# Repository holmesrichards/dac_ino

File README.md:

# dac/ino

This is a pair of boards and corresponding library which provide CV and gate I/O for an Arduino Nano. It is derived from [shaduzlabs/synapse](https://github.com/shaduzlabs/synapse), and there are obvious similarities to [ArdCore](http://20objects.com/ardcore/), but there are significant differences with both. 

There are two boards, dac/ino and dac/ino lite.

Differences between these and Synapse are:

- Board design with space for Arduino Nano, instead of as Uno style shield
- No on-board jacks — pads for Molex or pin connectors (or direct soldering) instead
- Simplification by eliminating software-controlled range selection
- Number of inputs and outputs is different
- dac/ino lite is battery powered and has 0–5 V output range, also uses Arduino Vcc as voltage reference

## Features
### dac/ino has
- 4 x control voltage inputs, 0 to 5V
- 2 x control voltage outputs, individually configurable as 0 to 5 V, 0 to 10 V, or -5 to 5 V via jumpers, with 12 bits of resolution
- 4 x gate inputs (with interrupt)
- 2 x gate outputs
- Additional inputs/outputs (direct connections to Arduino): 4 analog, 2 digital
- All above inputs/outputs connect via Molex connectors or solder pads, or via pin headers for daughterboards
- Voltage reference chip
- 1 x eurorack power connector (10 pin)

### dac/ino lite has
- 2 x control voltage outputs, 0 to 5 V, with 12 bits of resolution
- 1 x gate output
- Additional inputs/outputs (direct connections to Arduino): 4 analog, 2 digital
- All above inputs/outputs connect via Molex connectors or solder pads
- 6–12 V battery or unipolar power supply

## Compatible Arduinos
The PCB layout is for an Arduino Nano (5V).

## Dependencies
- [DirectIO](https://github.com/mmarchetti/DirectIO), for fast digital pin access

## Respository
- KiCad format schematics and PCB layouts, and Arduino library and example sketches, may be found at [https://github.com/holmesrichards/dac_ino](https://github.com/holmesrichards/dac_ino).

- [Build notes](docs/Build_notes.md)
- [dac/ino schematic](docs/dac_ino.pdf) (A bit confusing because the repetitive parts of the circuit are handled with KiCad heirarchical pages, so you have lots of pages with only a few components on each.)

- [dac/ino PCB layout](docs/dac_ino_pcb.pdf)

- [dac/ino BOM](docs/dac_ino_bom.md)

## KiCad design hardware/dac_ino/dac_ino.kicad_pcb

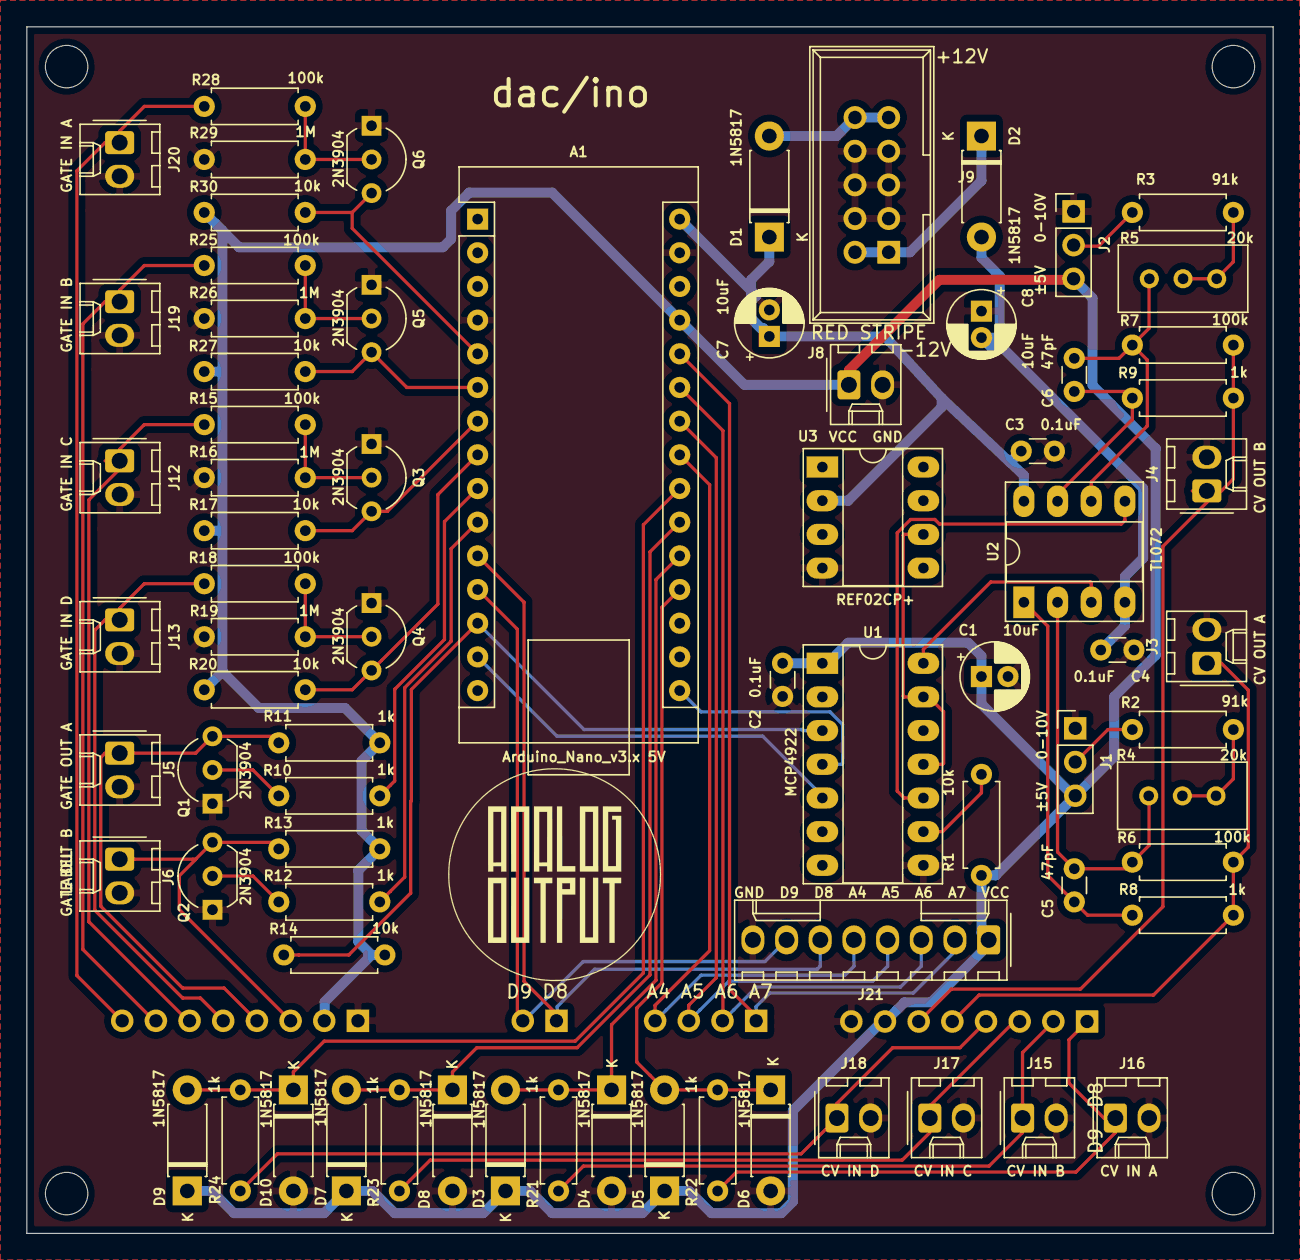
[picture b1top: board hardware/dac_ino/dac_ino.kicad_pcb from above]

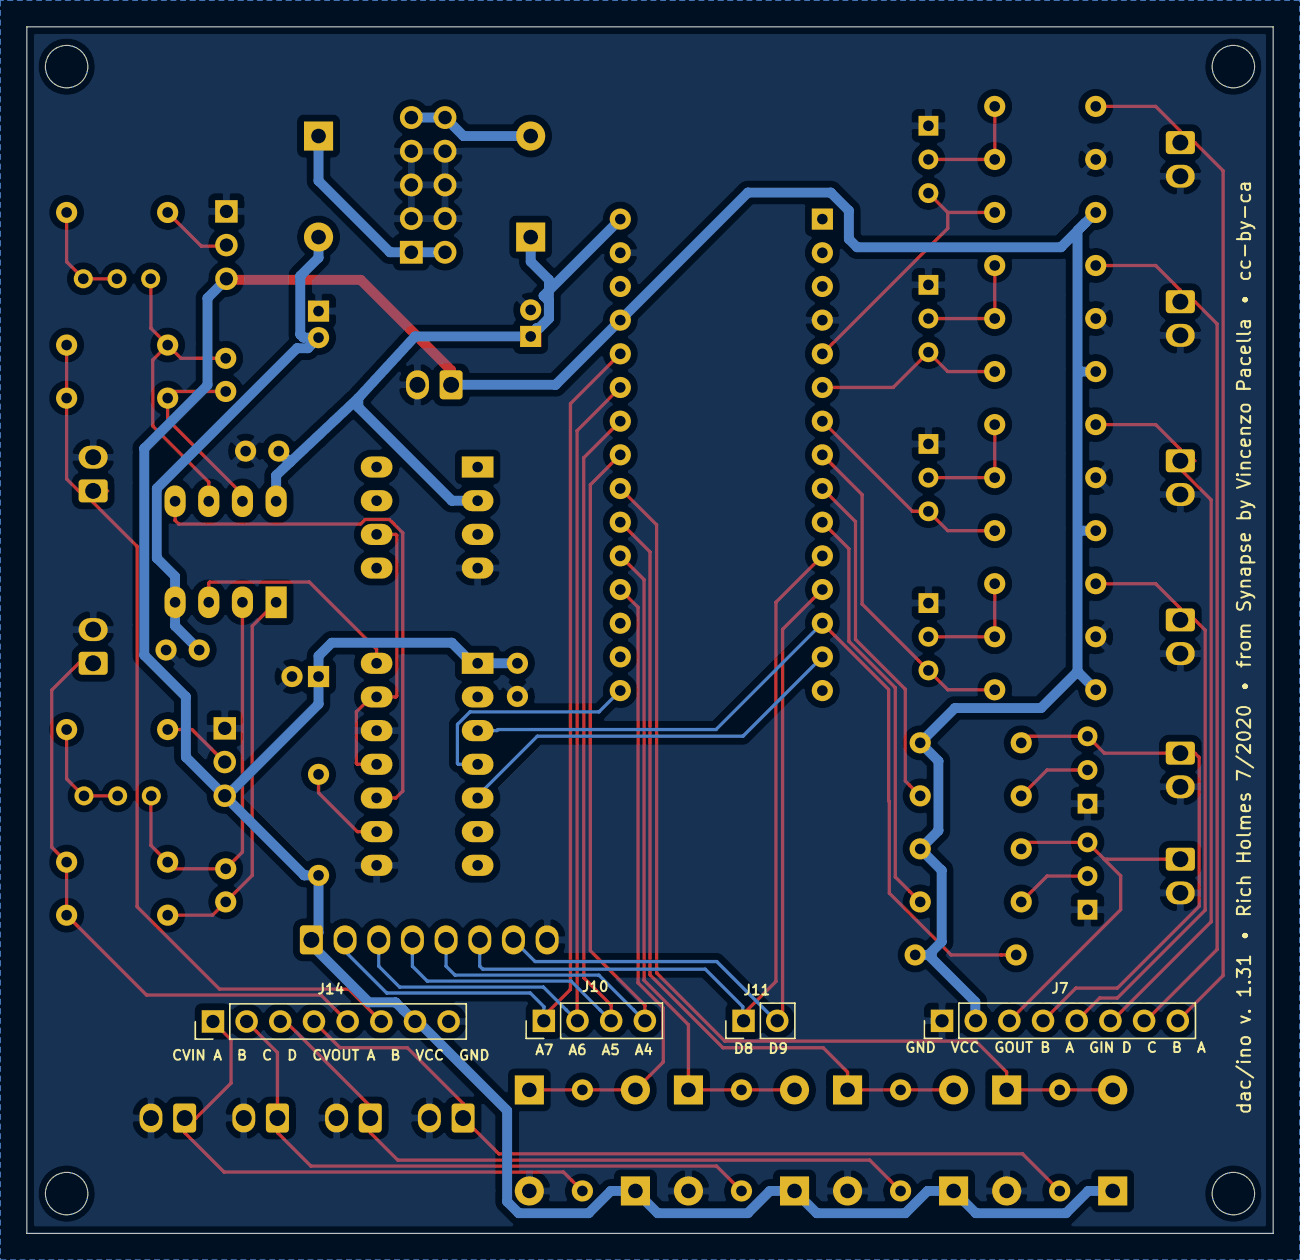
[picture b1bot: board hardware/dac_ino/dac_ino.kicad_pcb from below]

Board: 2 copper layers, 94.0 x 91.0 mm, 83 parts (4 on the bottom side), 55 nets.

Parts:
A1: Arduino_Nano_v3.x 5V; Arduino_Nano
C1, C7, C8: 10uF; CP_Radial_D5.0mm_P2.00mm
C2, C3, C4: 0.1uF; C_Disc_D3.0mm_W1.6mm_P2.50mm
C5, C6: 47pF; C_Disc_D3.0mm_W1.6mm_P2.50mm
D1, D2, D3, D4, D5, D6, D7, D8, D9, D10: 1N5817; D_DO-41_SOD81_P7.62mm_Horizontal
H1, H2, H3, H4: MountingHole; MountingHole_3.2mm_M3
J1, J2: Conn_01x03_Male; PinHeader_1x03_P2.54mm_Vertical
J3, J4: Molex 2 pin CV OUT; Molex_KK-254_AE-6410-02A_1x02_P2.54mm_Vertical
J5, J6: Molex 2 pin GATE OUT; Molex_KK-254_AE-6410-02A_1x02_P2.54mm_Vertical
J7, J14: Conn_01x01_Units; PinHeader_1x08_P2.54mm_Vertical
J8: Molex 2 pin VCC; Molex_KK-254_AE-6410-02A_1x02_P2.54mm_Vertical
J9: EURO_PWR_2x5; Power_Header
J10: Conn_01x04; PinHeader_1x04_P2.54mm_Vertical
J11: Conn_01x02; PinHeader_1x02_P2.54mm_Vertical
J12, J13, J19, J20: Molex 2 pin GATE IN; Molex_KK-254_AE-6410-02A_1x02_P2.54mm_Vertical
J15, J16, J17, J18: Molex 2 pin CV IN; Molex_KK-254_AE-6410-02A_1x02_P2.54mm_Vertical
J21: Conn_01x06; Molex_KK-254_AE-6410-08A_1x08_P2.54mm_Vertical
Q1, Q2, Q3, Q4, Q5, Q6: 2N3904; TO-92_Inline_Wide
R1, R14, R17, R20, R27, R30: 10k; R_Axial_DIN0207_L6.3mm_D2.5mm_P7.62mm_Horizontal
R2, R3: 91k; R_Axial_DIN0207_L6.3mm_D2.5mm_P7.62mm_Horizontal
R4, R5: 20k; Potentiometer_Bourns_3296W_Vertical
R6, R7, R15, R18, R25, R28: 100k; R_Axial_DIN0207_L6.3mm_D2.5mm_P7.62mm_Horizontal
R8, R9, R10, R11, R12, R13, R21, R22, R23, R24: 1k; R_Axial_DIN0207_L6.3mm_D2.5mm_P7.62mm_Horizontal
R16, R19, R26, R29: 1M; R_Axial_DIN0207_L6.3mm_D2.5mm_P7.62mm_Horizontal
U1: MCP4922; DIP-14_W7.62mm_Socket_LongPads
U2: TL072; DIP-8_W7.62mm_Socket_LongPads
U3: REF02CP+; DIP-8_W7.62mm_Socket_LongPads

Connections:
+VIN: A1.30, C3.1, C7.1, D1.1, U2.8, U3.2
-VIN: C4.2, C8.2, D2.2, U2.4
/Arduino/A0: A1.19, D5.2, D6.1, R22.1
/Arduino/A1: A1.20, D3.2, D4.1, R21.1
/Arduino/A2: A1.21, D7.2, D8.1, R23.1
/Arduino/A3: A1.22, D9.2, D10.1, R24.1
/Arduino/A4: A1.23, J10.4, J21.5
/Arduino/A5: A1.24, J10.3, J21.4
/Arduino/A6: A1.25, J10.2, J21.3
/Arduino/A7: A1.26, J10.1, J21.2
/Arduino/D2: A1.5, Q6.3, R30.1
/Arduino/D3: A1.6, Q5.3, R27.1
/Arduino/D4: A1.7, Q3.3, R17.1
/Arduino/D5: A1.8, Q4.3, R20.1
/Arduino/D6: A1.9, R10.2
/Arduino/D7: A1.10, R12.2
/Arduino/D8: A1.11, J11.1, J21.6
/Arduino/D9: A1.12, J11.2, J21.7
/Arduino/DAC_CS: A1.13, R14.2, U1.3
/Arduino/MOSI: A1.14, U1.5
/Arduino/SCK: A1.16, U1.4
/CV out/CV_OUT_A: J3.1, J14.5, R6.2, R8.2
/CV out/CV_OUT_B: J4.1, J14.6, R7.2, R9.2
/CV out/DAC_A: U1.14, U2.3
/CV out/DAC_B: U1.10, U2.5
/Gate out/GATE_OUT_A: J5.1, J7.4, Q1.3, R11.1
/Gate out/GATE_OUT_B: J6.1, J7.3, Q2.3, R13.1
/Inputs/CV IN D/CV_IN: J14.4, J18.1, R24.2
/Inputs/CV in A/CV_IN: J14.1, J16.1, R22.2
/Inputs/CV in B/CV_IN: J14.2, J15.1, R21.2
/Inputs/CV in C/CV_IN: J14.3, J17.1, R23.2
/Inputs/Gate in A/GATE_IN: J7.8, J20.1, R28.2
/Inputs/Gate in B/GATE_IN: J7.7, J19.1, R25.2
/Inputs/Gate in C/GATE_IN: J7.6, J12.1, R15.2
/Inputs/Gate in D/GATE_IN: J7.5, J13.1, R18.2
/Voltage reference/VREF: U1.11, U1.13, U3.6
GND: A1.4, A1.29, C1.2, C2.2, C3.2, C4.1, C7.2, C8.1, D4.2, D6.2, D8.2, D10.2, J1.1, J2.1, J3.2, J4.2, J5.2, J6.2, J7.1, J8.2, J9.3, J9.4, J9.5, J9.6, J9.7, J9.8, J12.2, J13.2, J14.8, J15.2, J16.2, J17.2, J18.2, J19.2, J20.2, J21.8, Q1.1, Q2.1, Q3.1, Q4.1, Q5.1, Q6.1, R16.1, R19.1, R26.1, R29.1, U1.8, U1.12, U3.4
unnamed: C5.1, R8.1, U2.1
unnamed: C5.2, R4.1, R6.1, U2.2
unnamed: C6.1, R9.1, U2.7
unnamed: C6.2, R5.1, R7.1, U2.6
unnamed: D1.2, J9.9, J9.10
unnamed: D2.1, J9.1, J9.2
unnamed: J1.2, R2.1
unnamed: J2.2, R3.1
unnamed: Q1.2, R10.1
unnamed: Q2.2, R12.1
unnamed: Q3.2, R15.1, R16.2
unnamed: Q4.2, R18.1, R19.2
unnamed: Q5.2, R25.1, R26.2
unnamed: Q6.2, R28.1, R29.2
unnamed: R1.2, U1.9
unnamed: R2.2, R4.2, R4.3
unnamed: R3.2, R5.2, R5.3
VCC: A1.27, C1.1, C2.1, D3.1, D5.1, D7.1, D9.1, J1.3, J2.3, J7.2, J8.1, J14.7, J21.1, R1.1, R11.2, R13.2, R14.1, R17.2, R20.2, R27.2, R30.2, U1.1

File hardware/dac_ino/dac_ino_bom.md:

# dac_ino BOM

Mon 04 May 2020 10:14:20 AM EDT

Generated from schematic by Eeschema 5.1.5-52549c5~84~ubuntu18.04.1

**Component Count:** 79

| Value | Qty | Part | Description | Vendor |
| ----- | --- | ---- | ----------- | ------ |
| A1 | 1 | Arduino_Nano_v3.x 5V | Arduino Nano v3.x |  |
| C1, C7, C8 | 3 | 10uF | Polarized capacitor |  |
| C2, C3, C4 | 3 | 0.1uF | Unpolarized capacitor |  |
| C5, C6 | 2 | 47pF | Unpolarized capacitor |  |
| D1, D2, D3, D4, D5, D6, D7, D8, D9, D10 | 10 | 1N5817 | 20V 1A Schottky Barrier Rectifier Diode, DO-41 |  |
| H1, H2, H3, H4 | 4 | MountingHole | Mounting Hole without connection |  |
| J1, J2 | 2 | Conn_01x03_Male | Generic connector, single row, 01x03, script generated (kicad-library-utils/schlib/autogen/connector/) |  |
| J3, J4, J5, J6 | 4 | Molex 2 pin | Generic connector, single row, 01x02, script generated (kicad-library-utils/schlib/autogen/connector/) |  |
| J7 | 1 | VCC | Generic connector, single row, 01x02, script generated (kicad-library-utils/schlib/autogen/connector/) |  |
| J8 | 1 | EURO_PWR_2x5 |  |  |
| J9 | 1 | Conn_01x04 | Generic connector, single row, 01x04, script generated (kicad-library-utils/schlib/autogen/connector/) |  |
| J10 | 1 | Conn_01x02 | Generic connector, single row, 01x02, script generated (kicad-library-utils/schlib/autogen/connector/) |  |
| J11, J12, J13, J14 | 4 | GATE IN | Generic connector, single row, 01x02, script generated (kicad-library-utils/schlib/autogen/connector/) |  |
| J15, J16, J17, J18 | 4 | CV IN | Generic connector, single row, 01x02, script generated (kicad-library-utils/schlib/autogen/connector/) |  |
| Q1, Q2, Q3, Q4, Q5, Q6 | 6 | 2N3904 | 0.2A Ic, 40V Vce, Small Signal NPN Transistor, TO-92 |  |
| R1, R14, R17, R20, R23, R26 | 6 | 10k | Resistor |  |
| R2, R3 | 2 | 91k | Resistor |  |
| R4, R5 | 2 | 20k | Trim-potentiometer |  |
| R6, R7, R15, R18, R21, R24 | 6 | 100k | Resistor |  |
| R8, R9, R10, R11, R12, R13, R27, R28, R29, R30 | 10 | 1k | Resistor |  |
| R16, R19, R22, R25 | 4 | 1M | Resistor |  |
| U1 | 1 | MCP4922 | 2-Channel 12-Bit D/A Converters with SPI Interface |  |
| U2 | 1 | TL072 | Dual Low-Noise JFET-Input Operational Amplifiers, DIP-8/SOIC-8 |  |

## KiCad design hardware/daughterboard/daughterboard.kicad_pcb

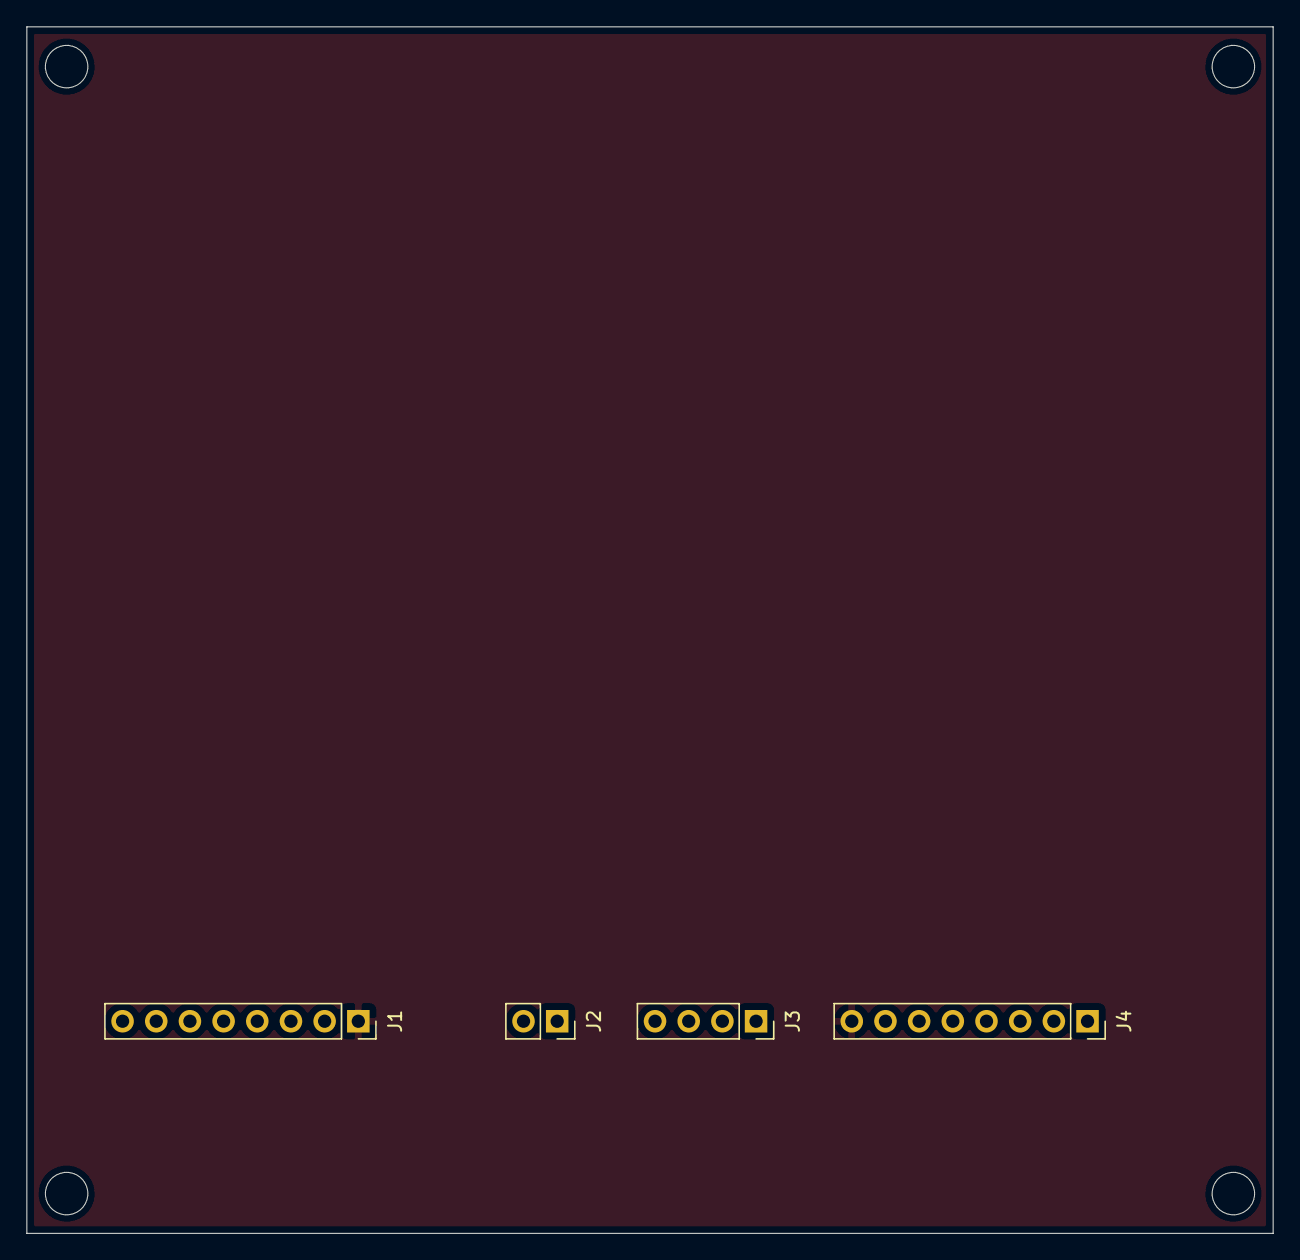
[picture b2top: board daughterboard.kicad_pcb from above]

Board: 2 copper layers, 94.0 x 91.0 mm, 8 parts (0 on the bottom side), 2 nets, no tracks yet.

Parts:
H1, H2, H3, H4: MountingHole; MountingHole_3.2mm_M3
J1, J4: Conn_01x08; PinSocket_1x08_P2.54mm_Vertical
J2: Conn_01x02; PinSocket_1x02_P2.54mm_Vertical
J3: Conn_01x04; PinSocket_1x04_P2.54mm_Vertical

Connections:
GND: J1.1, J4.8
VCC: J1.2, J4.7

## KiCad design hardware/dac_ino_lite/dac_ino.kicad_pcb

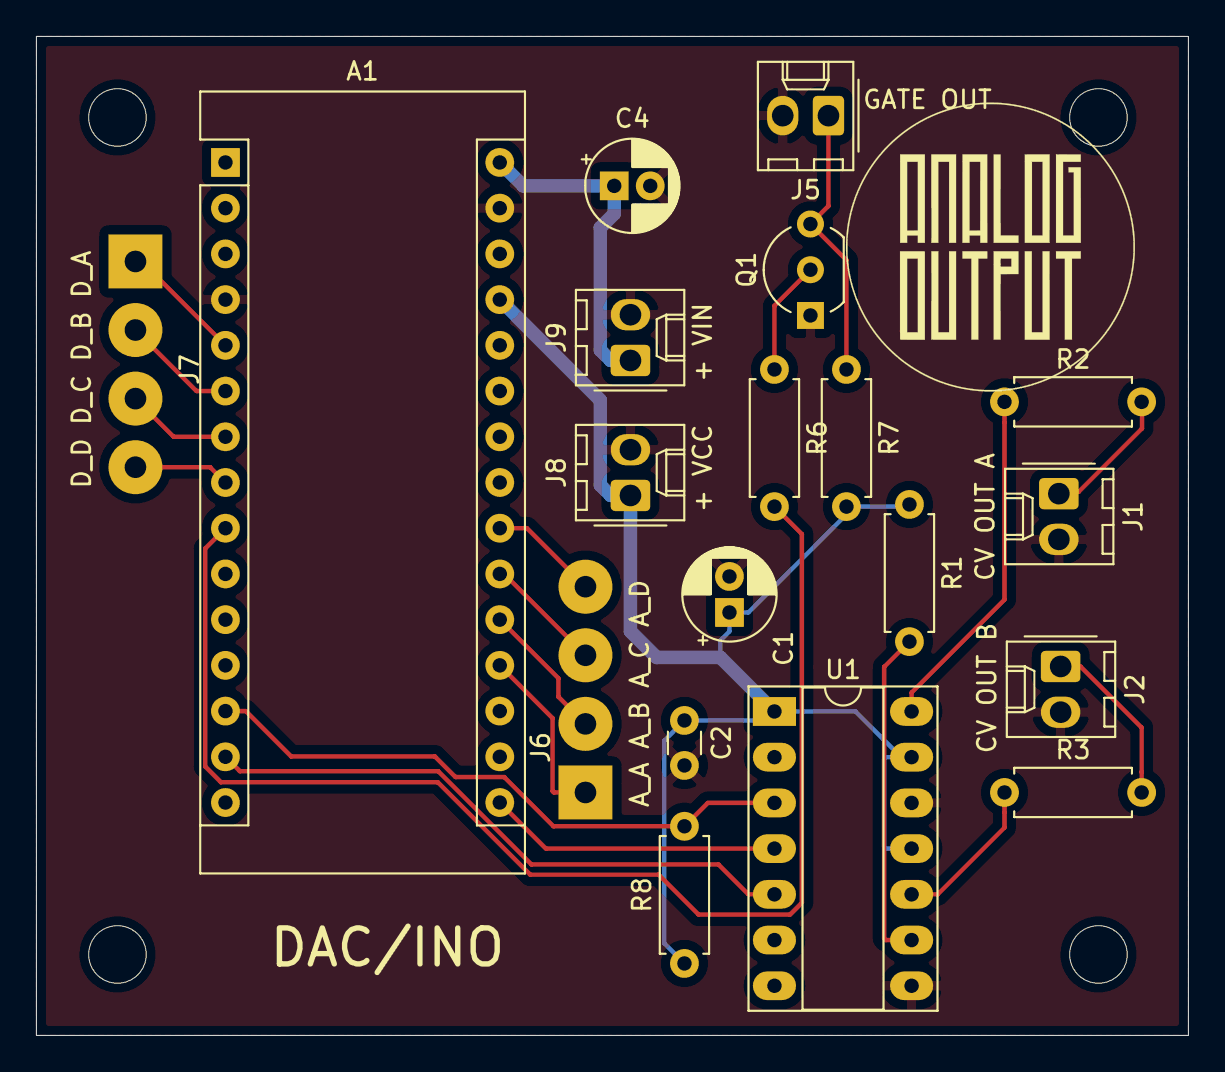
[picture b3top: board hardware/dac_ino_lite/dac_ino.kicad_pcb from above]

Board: 2 copper layers, 64.0 x 55.5 mm, 23 parts (0 on the bottom side), 22 nets.

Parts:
A1: Arduino_Nano_v3.x 5V; Arduino_Nano
C1, C4: 10uF; CP_Radial_D5.0mm_P2.00mm
C2: 0.1uF; C_Disc_D3.0mm_W1.6mm_P2.50mm
H1, H2, H3, H4: MountingHole; MountingHole_3.2mm_M3
J1: CV OUT A; Molex_KK-254_AE-6410-02A_1x02_P2.54mm_Vertical
J2: CV OUT B; Molex_KK-254_AE-6410-02A_1x02_P2.54mm_Vertical
J5: GATE OUT A; Molex_KK-254_AE-6410-02A_1x02_P2.54mm_Vertical
J6, J7: Conn_01x04; SolderWirePad_1x04_P3.81mm_Drill1.2mm
J8: VCC; Molex_KK-254_AE-6410-02A_1x02_P2.54mm_Vertical
J9: Vin; Molex_KK-254_AE-6410-02A_1x02_P2.54mm_Vertical
Q1: 2N3904; TO-92_Inline_Wide
R1, R8: 10K; R_Axial_DIN0207_L6.3mm_D2.5mm_P7.62mm_Horizontal
R2, R3: 1K; R_Axial_DIN0207_L6.3mm_D2.5mm_P7.62mm_Horizontal
R6, R7: 1k; R_Axial_DIN0207_L6.3mm_D2.5mm_P7.62mm_Horizontal
U1: MCP4922; DIP-14_W7.62mm_Socket_LongPads

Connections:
+VIN: A1.30, C4.1, J9.1
/Arduino/A_IN_A: A1.19, J6.1
/Arduino/A_IN_B: A1.20, J6.2
/Arduino/A_IN_C: A1.21, J6.3
/Arduino/A_IN_D: A1.22, J6.4
/Arduino/DAC_CS: A1.13, R8.2, U1.3
/Arduino/D_IN_A: A1.5, J7.1
/Arduino/D_IN_B: A1.6, J7.2
/Arduino/D_IN_C: A1.7, J7.3
/Arduino/D_IN_D: A1.8, J7.4
/Arduino/D_OUT_A: A1.9, R6.2
/Arduino/MOSI: A1.14, U1.5
/Arduino/SCK: A1.16, U1.4
/DAC/CV_OUT_A: J1.1, R2.2
/DAC/CV_OUT_B: J2.1, R3.2
/Gate out/GATE_OUT: J5.1, Q1.3, R7.1
GND: A1.4, A1.29, C1.2, C2.2, C4.2, J1.2, J2.2, J5.2, J8.2, J9.2, Q1.1, U1.8, U1.12
unnamed: Q1.2, R6.1
unnamed: R1.2, U1.9
unnamed: R2.1, U1.14
unnamed: R3.1, U1.10
VCC: A1.27, C1.1, C2.1, J8.1, R1.1, R7.2, R8.1, U1.1, U1.11, U1.13

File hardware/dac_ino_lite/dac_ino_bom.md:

# dac_ino BOM

Mon 04 May 2020 10:25:07 AM EDT

Generated from schematic by Eeschema 5.1.5-52549c5~84~ubuntu18.04.1

**Component Count:** 23

| Value | Qty | Part | Description | Vendor |
| ----- | --- | ---- | ----------- | ------ |
| A1 | 1 | Arduino_Nano_v3.x 5V | Arduino Nano v3.x |  |
| C1, C4 | 2 | 10uF | Polarized capacitor |  |
| C2 | 1 | 0.1uF | Unpolarized capacitor |  |
| H1, H2, H3, H4 | 4 | MountingHole | Mounting Hole without connection |  |
| J1 | 1 | CV OUT A | Generic connector, single row, 01x02, script generated (kicad-library-utils/schlib/autogen/connector/) |  |
| J2 | 1 | CV OUT B | Generic connector, single row, 01x02, script generated (kicad-library-utils/schlib/autogen/connector/) |  |
| J5 | 1 | GATE OUT A | Generic connector, single row, 01x02, script generated (kicad-library-utils/schlib/autogen/connector/) |  |
| J6, J7 | 2 | Conn_01x04 | Generic connector, single row, 01x04, script generated (kicad-library-utils/schlib/autogen/connector/) |  |
| J8 | 1 | VCC | Generic connector, single row, 01x02, script generated (kicad-library-utils/schlib/autogen/connector/) |  |
| J9 | 1 | Vin | Generic connector, single row, 01x02, script generated (kicad-library-utils/schlib/autogen/connector/) |  |
| Q1 | 1 | 2N3904 | 0.2A Ic, 40V Vce, Small Signal NPN Transistor, TO-92 |  |
| R1, R8 | 2 | 10k | Resistor |  |
| R2, R3, R6, R7 | 4 | 1k | Resistor |  |
| U1 | 1 | MCP4922 | 2-Channel 12-Bit D/A Converters with SPI Interface |  |

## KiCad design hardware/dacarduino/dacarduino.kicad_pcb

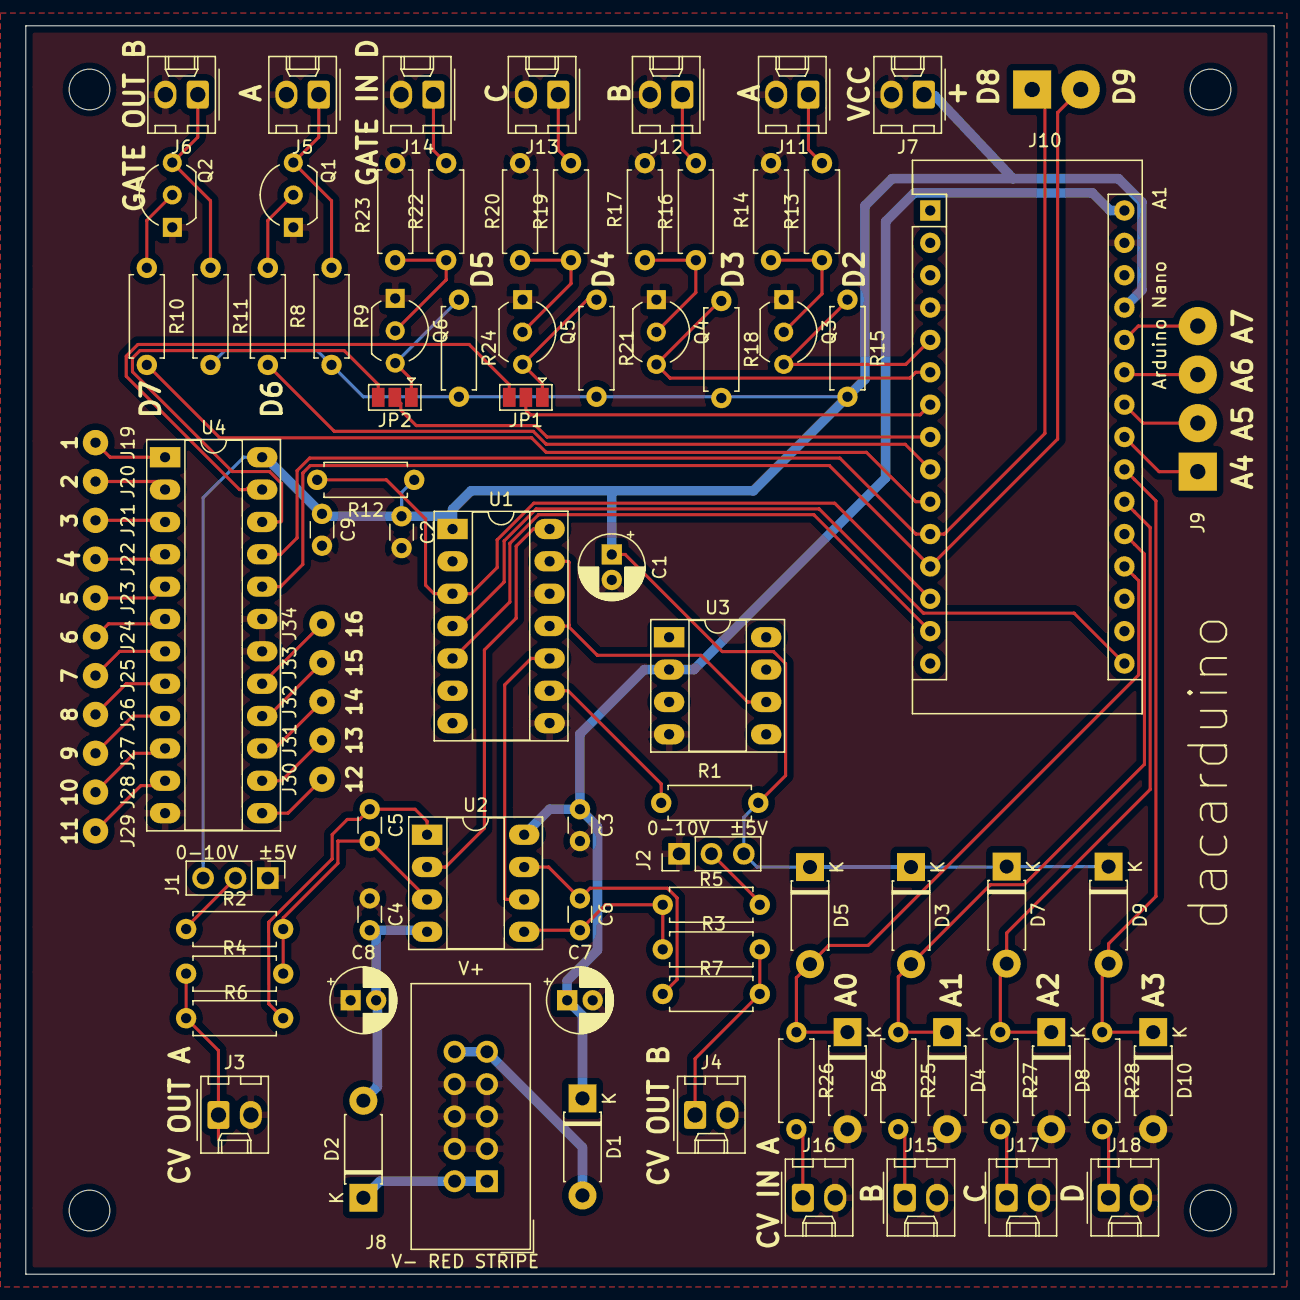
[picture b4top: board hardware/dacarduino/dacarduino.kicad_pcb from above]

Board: 2 copper layers, 98.0 x 98.0 mm, 98 parts (0 on the bottom side), 73 nets.

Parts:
A1: Arduino_Nano_v3.x 5V; Arduino_Nano
C1, C7, C8: 10uF; CP_Radial_D5.0mm_P2.00mm
C2, C3, C4, C9: 0.1uF; C_Disc_D3.0mm_W1.6mm_P2.50mm
C5, C6: 47pF; C_Disc_D3.0mm_W1.6mm_P2.50mm
D1, D2, D3, D4, D5, D6, D7, D8, D9, D10: 1N5817; D_DO-41_SOD81_P7.62mm_Horizontal
H1, H2, H3, H4: MountingHole; MountingHole_3.2mm_M3
J1, J2: Conn_01x03_Male; PinHeader_1x03_P2.54mm_Vertical
J3, J4, J5, J6: Molex 2 pin; Molex_KK-254_AE-6410-02A_1x02_P2.54mm_Vertical
J7: VCC; Molex_KK-254_AE-6410-02A_1x02_P2.54mm_Vertical
J8: EURO_PWR_2x5; IDC-Header_2x05_P2.54mm_Vertical
J9: Conn_01x04; SolderWirePad_1x04_P3.81mm_Drill1.2mm
J10: Conn_01x02; SolderWirePad_1x02_P3.81mm_Drill1.2mm
J11, J12, J13, J14: GATE IN; Molex_KK-254_AE-6410-02A_1x02_P2.54mm_Vertical
J15, J16, J17, J18: CV IN; Molex_KK-254_AE-6410-02A_1x02_P2.54mm_Vertical
J19, J20, J21, J22, J23, J24, J25, J26, J27, J28, J29, J30, J31, J32, J33, J34: Conn_01x01; SolderWirePad_1x01_Drill0.8mm
JP1, JP2: SolderJumper_3_Open; SolderJumper-3_P1.3mm_Open_Pad1.0x1.5mm
Q1, Q2, Q3, Q4, Q5, Q6: 2N3904; TO-92_Inline_Wide
R1, R12: 10K; R_Axial_DIN0207_L6.3mm_D2.5mm_P7.62mm_Horizontal
R2, R3, R4, R5: 100K; R_Axial_DIN0207_L6.3mm_D2.5mm_P7.62mm_Horizontal
R6, R7: 1K; R_Axial_DIN0207_L6.3mm_D2.5mm_P7.62mm_Horizontal
R8, R9, R10, R11, R25, R26, R27, R28: 1k; R_Axial_DIN0207_L6.3mm_D2.5mm_P7.62mm_Horizontal
R13, R16, R19, R22: 100k; R_Axial_DIN0207_L6.3mm_D2.5mm_P7.62mm_Horizontal
R14, R17, R20, R23: 1M; R_Axial_DIN0207_L6.3mm_D2.5mm_P7.62mm_Horizontal
R15, R18, R21, R24: 10k; R_Axial_DIN0207_L6.3mm_D2.5mm_P7.62mm_Horizontal
U1: MCP4922; DIP-14_W7.62mm_Socket_LongPads
U2: TL072; DIP-8_W7.62mm_Socket_LongPads
U3: REF02CP+; DIP-8_W7.62mm_Socket_LongPads
U4: SN74LS154N; DIP-24_W7.62mm_Socket_LongPads

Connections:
+VIN: A1.30, C3.1, C7.1, D1.1, U2.8, U3.2
-VIN: C4.2, C8.2, D2.2, U2.4
/Arduino/A0: A1.19, D5.2, D6.1, R26.1
/Arduino/A1: A1.20, D3.2, D4.1, R25.1
/Arduino/A2: A1.21, D7.2, D8.1, R27.1
/Arduino/A3: A1.22, D9.2, D10.1, R28.1
/Arduino/A4: A1.23, J9.1
/Arduino/A5: A1.24, J9.2
/Arduino/A6: A1.25, J9.3
/Arduino/A7: A1.26, J9.4
/Arduino/D2: A1.5, Q3.3, R15.1
/Arduino/D3: A1.6, Q4.3, R18.1
/Arduino/D4: A1.7, JP1.2
/Arduino/D5: A1.8, JP2.2
/Arduino/D6: A1.9, R8.2
/Arduino/D7: A1.10, R10.2
/Arduino/D8: A1.11, J10.1, U4.21
/Arduino/D9: A1.12, J10.2, U4.20
/Arduino/DAC_CS: A1.13, R12.2, U1.3
/Arduino/MOSI: A1.14, U1.5
/Arduino/SCK: A1.16, U1.4
/CV out/CV_OUT_A: J3.1, R4.2, R6.2
/CV out/CV_OUT_B: J4.1, R5.2, R7.2
/CV out/DAC_A: U1.14, U2.2
/CV out/DAC_B: U1.10, U2.6
/Gate out/GATE_OUT_A: J5.1, Q1.3, R9.1
/Gate out/GATE_OUT_B: J6.1, Q2.3, R11.1
/Inputs/CV IN D/CV_IN: J18.1, R28.2
/Inputs/CV in A/CV_IN: J16.1, R26.2
/Inputs/CV in B/CV_IN: J15.1, R25.2
/Inputs/CV in C/CV_IN: J17.1, R27.2
/Inputs/Gate in A/GATE_IN: J11.1, R13.2
/Inputs/Gate in B/GATE_IN: J12.1, R16.2
/Inputs/Gate in C/D_IN: JP1.1, Q5.3, R21.1
/Inputs/Gate in C/GATE_IN: J13.1, R19.2
/Inputs/Gate in D/D_IN: JP2.1, Q6.3, R24.1
/Inputs/Gate in D/GATE_IN: J14.1, R22.2
/Voltage reference/VREF: U1.11, U1.13, U3.6
GND: A1.4, A1.29, C1.2, C2.2, C3.2, C4.1, C7.2, C8.1, C9.2, D4.2, D6.2, D8.2, D10.2, J1.1, J2.1, J3.2, J4.2, J5.2, J6.2, J7.2, J8.3, J8.4, J8.5, J8.6, J8.7, J8.8, J11.2, J12.2, J13.2, J14.2, J15.2, J16.2, J17.2, J18.2, Q1.1, Q2.1, Q3.1, Q4.1, Q5.1, Q6.1, R14.1, R17.1, R20.1, R23.1, U1.8, U1.12, U3.4, U4.12, U4.18, U4.19
unnamed: C5.1, R6.1, U2.1
unnamed: C5.2, R2.2, R4.1, U2.3
unnamed: C6.1, R7.1, U2.7
unnamed: C6.2, R3.2, R5.1, U2.5
unnamed: D1.2, J8.9, J8.10
unnamed: D2.1, J8.1, J8.2
unnamed: J1.2, R2.1
unnamed: J2.2, R3.1
unnamed: J19.1, U4.1
unnamed: J20.1, U4.2
unnamed: J21.1, U4.3
unnamed: J22.1, U4.4
unnamed: J23.1, U4.5
unnamed: J24.1, U4.6
unnamed: J25.1, U4.7
unnamed: J26.1, U4.8
unnamed: J27.1, U4.9
unnamed: J28.1, U4.10
unnamed: J29.1, U4.11
unnamed: J30.1, U4.13
unnamed: J31.1, U4.14
unnamed: J32.1, U4.15
unnamed: J33.1, U4.16
unnamed: J34.1, U4.17
unnamed: JP1.3, U4.23
unnamed: JP2.3, U4.22
unnamed: Q1.2, R8.1
unnamed: Q2.2, R10.1
unnamed: Q3.2, R13.1, R14.2
unnamed: Q4.2, R16.1, R17.2
unnamed: Q5.2, R19.1, R20.2
unnamed: Q6.2, R22.1, R23.2
unnamed: R1.2, U1.9
VCC: A1.27, C1.1, C2.1, C9.1, D3.1, D5.1, D7.1, D9.1, J1.3, J2.3, J7.1, R1.1, R9.2, R11.2, R12.1, R15.2, R18.2, R21.2, R24.2, U1.1, U4.24

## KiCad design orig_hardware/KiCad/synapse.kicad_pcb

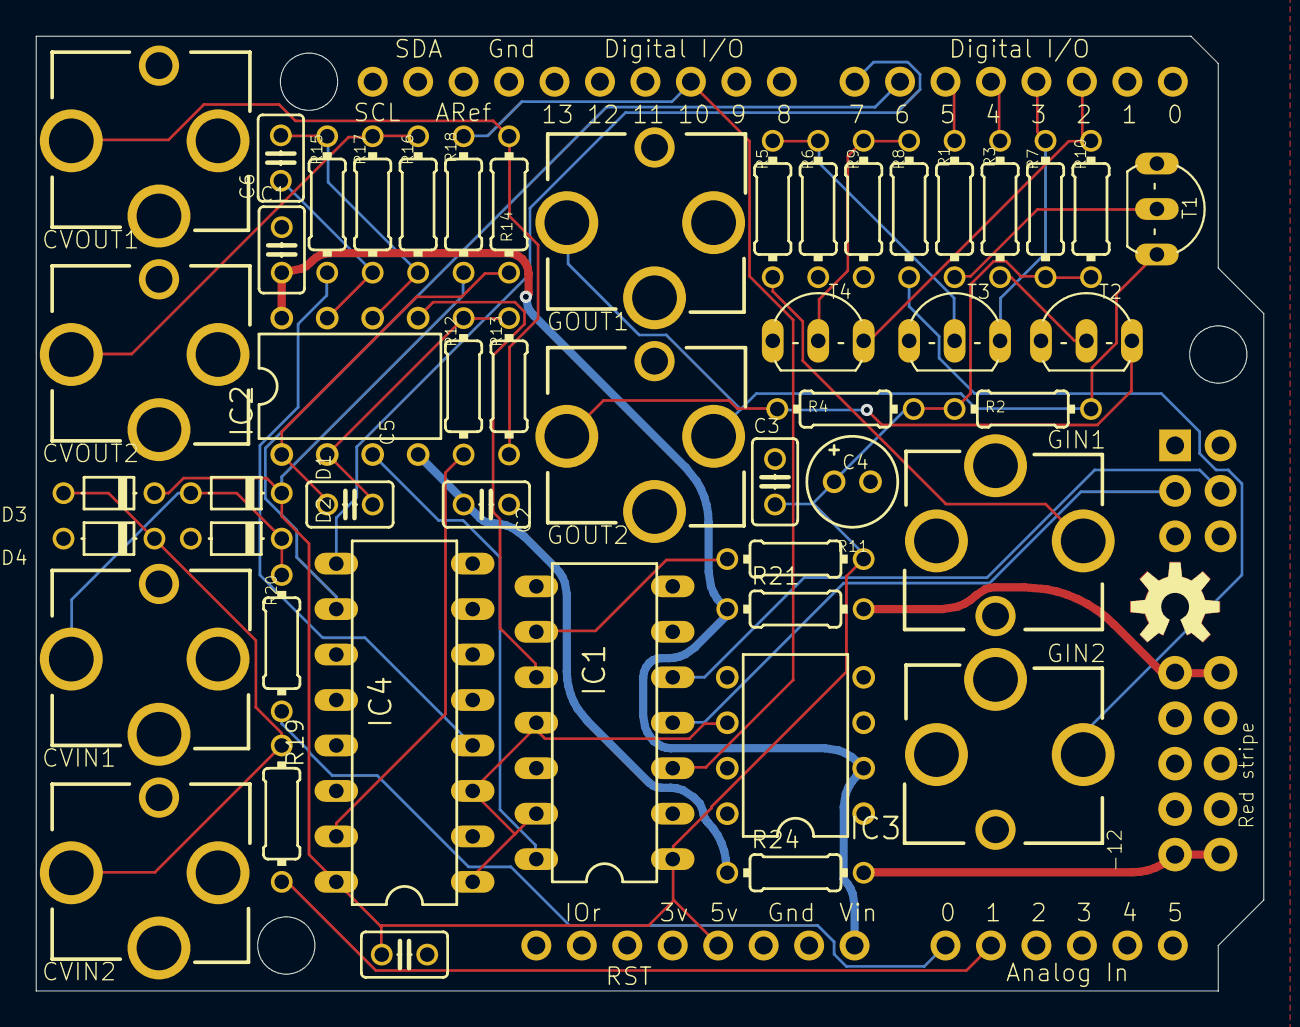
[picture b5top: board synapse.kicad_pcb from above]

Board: 2 copper layers, 68.6 x 53.3 mm, 56 parts (0 on the bottom side), 39 nets.

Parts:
@HOLE0, @HOLE1, @HOLE2: (no value)
C1, C2, C3, C7: 100n; C025-025X050
C4: 10u; E2-5
C5, C6: 47p; C025-025X050
CVIN1, CVIN2: AUDIO-JACKERTHENVAR; ERTHENVAR-JACK
CVOUT1, CVOUT2: AUDIO-JACKERTHENVAR; ERTHENVAR-JACK
D1, D2, D3, D4: BAT85; D-5
GIN1, GIN2: AUDIO-JACKERTHENVAR; ERTHENVAR-JACK
GOUT1, GOUT2: AUDIO-JACKERTHENVAR; ERTHENVAR-JACK
IC1: MCP4922E_P; DIL14
IC2: TL072P; DIL08
IC3: REF02CP; DIL08
IC4: 4053N; DIL16
M1: ARDUINO_R3_ICSP; ARDUINOR3_ICSP
R1, R2, R3, R4, R14, R17, R19, R20: 1K; 0204_7
R5, R8, R12, R13, R15, R16: 100K; 0204_7
R6, R9: 1M; 0204_7
R7, R10, R11, R18: 10K; 0204_7
R21, R24: BEAD; 0204_7
T1, T2, T3, T4: 2N3904; TO92-EBC
U$1: OSHWLOGO_TOP_0.2
U$2: POWER_SIMPLE10; POWER_10
U$3: OSHW-LOGO-M

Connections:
/synapse_1/12V: C1.1, IC2.8, IC3.2, M1.VIN, R21.1
/synapse_1/-12V: C2.1, IC2.4, R24.1
/synapse_1/DAC_A: IC1.14, IC2.3
/synapse_1/DAC_B: IC1.10, IC2.5
/synapse_1/DAC_CS: IC1.3, M1.D10, R18.1
/synapse_1/MOSI: IC1.5, M1.MOSI
/synapse_1/SCK: IC1.4, M1.SCK
/synapse_2/GATE_IN_A: GIN1.3, R5.1
/synapse_2/GATE_IN_B: GIN2.3, R8.1
/synapse_2/GATE_OUT_A: GOUT1.3, GOUT2.2, R2.1, T1.C
/synapse_2/GATE_OUT_B: GOUT2.3, R4.1, T2.C
CFG_A: IC4.10, M1.D6
CFG_B: IC4.9, M1.D7
CV_IN_A: CVIN1.3, D1.A, D2.C, R20.1
CV_IN_B: CVIN2.3, D3.A, D4.C, R19.1
CV_OUT_A: CVOUT1.3, R13.1, R14.1
CV_OUT_B: CVOUT2.3, R16.1, R17.1
D_IN_A: M1.D3, R7.1, T3.C
D_IN_B: M1.D2, R10.1, T4.C
D_OUT_A: M1.D5, R1.1
D_OUT_B: M1.D4, R3.1
GND: C1.2, C2.2, C3.2, C4.-, C7.2, CVIN1.1@1, CVIN1.1@2, CVIN1.2, CVIN2.1@1, CVIN2.1@2, CVIN2.2, CVOUT1.1@1, CVOUT1.1@2, CVOUT2.1@1, CVOUT2.1@2, D2.A, D4.A, GIN1.1@1, GIN1.1@2, GIN1.2, GIN2.1@1, GIN2.1@2, GIN2.2, GOUT1.1@1, GOUT1.1@2, GOUT2.1@1, GOUT2.1@2, IC1.8, IC1.12, IC3.4, IC4.2, IC4.5, IC4.6, IC4.7, IC4.8, IC4.11, IC4.12, IC4.13, M1.GND, M1.GND@1, M1.GND@3, R6.1, R9.1, T1.E, T2.E, T3.E, T4.E, U$2.3, U$2.4, U$2.5, U$2.6, U$2.7, U$2.8
unnamed: C5.1, IC2.2, R12.1, R13.2
unnamed: C5.2, IC2.1, R14.2
unnamed: C6.1, IC2.6, R15.1, R16.2
unnamed: C6.2, IC2.7, R17.2
unnamed: IC1.9, R11.2
unnamed: M1.A0, R20.2
unnamed: M1.A1, R19.2
unnamed: R1.2, T1.B
unnamed: R3.2, T2.B
unnamed: R5.2, R6.2, T3.B
unnamed: R8.2, R9.2, T4.B
unnamed: R21.2, U$2.9, U$2.10
unnamed: R24.2, U$2.1, U$2.2
OFFSET_A: IC4.15, R12.2
OFFSET_B: IC4.4, R15.2
VCC: C3.1, C4.+, C7.1, D1.C, D3.C, IC1.1, IC4.16, M1.5V, R2.2, R4.2, R7.2, R10.2, R11.1, R18.2
VREF: IC1.11, IC1.13, IC3.6, IC4.1, IC4.3

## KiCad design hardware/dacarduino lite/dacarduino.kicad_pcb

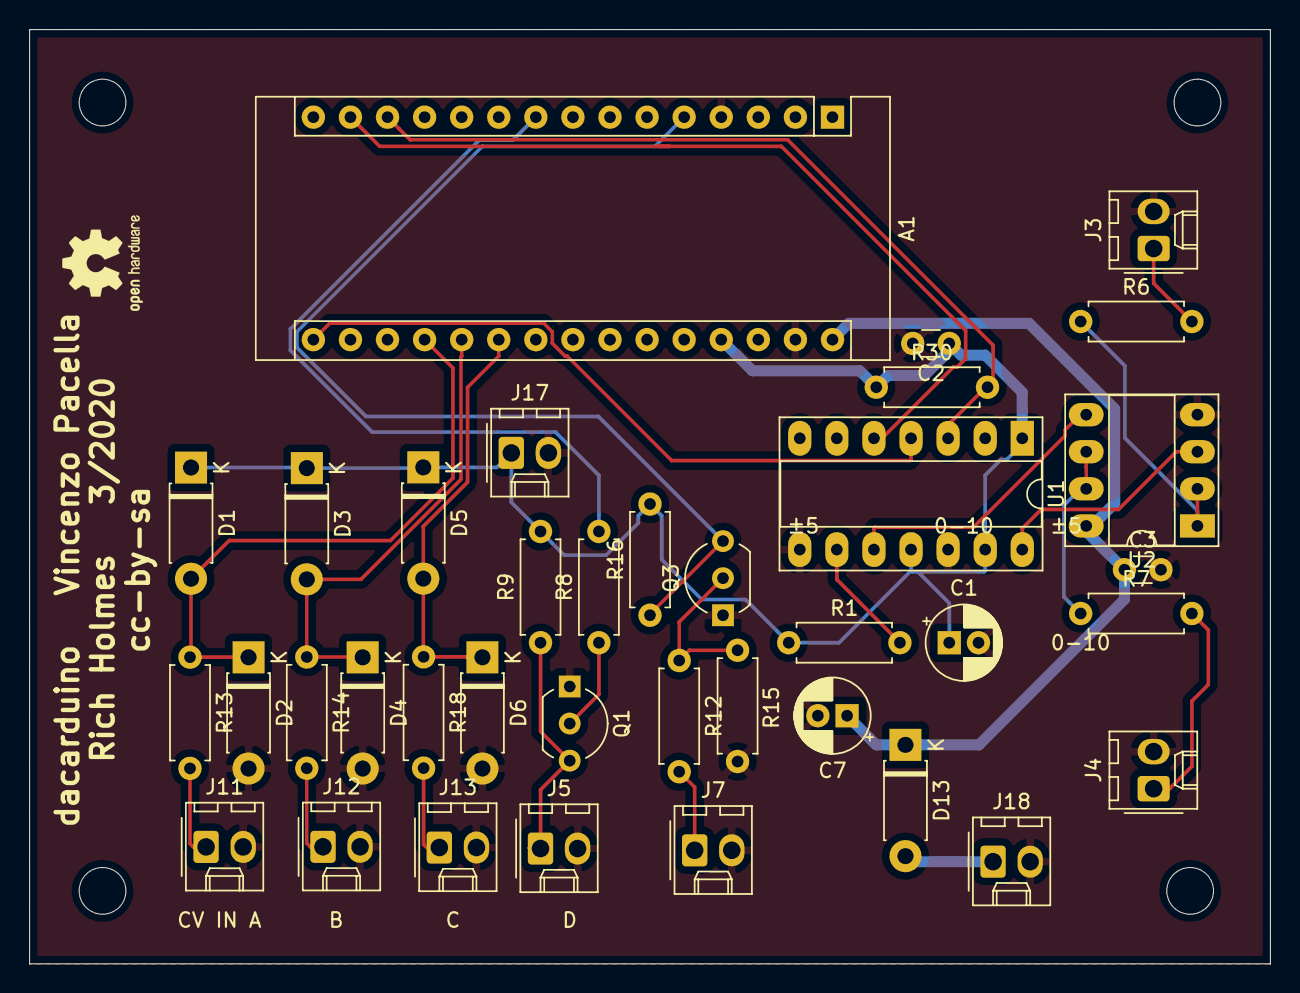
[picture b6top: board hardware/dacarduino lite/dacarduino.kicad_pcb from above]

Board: 2 copper layers, 85.0 x 64.0 mm, 41 parts (0 on the bottom side), 26 nets.

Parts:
A1: Arduino_Nano_v3.x 5V; Arduino_Nano
C1, C7: 10uF; CP_Radial_D5.0mm_P2.00mm
C2, C3: 0.1uF; C_Disc_D3.0mm_W1.6mm_P2.50mm
D1, D2, D3, D4, D5, D6, D13: 1N5817; D_DO-41_SOD81_P7.62mm_Horizontal
H1, H2, H3, H4: MountingHole; MountingHole_3.2mm_M3
J3: CV OUT A; Molex_KK-254_AE-6410-02A_1x02_P2.54mm_Vertical
J4: CV OUT B; Molex_KK-254_AE-6410-02A_1x02_P2.54mm_Vertical
J5: GATE OUT A; Molex_KK-254_AE-6410-02A_1x02_P2.54mm_Vertical
J7: GATE IN; Molex_KK-254_AE-6410-02A_1x02_P2.54mm_Vertical
J11, J12, J13: CV IN; Molex_KK-254_AE-6410-02A_1x02_P2.54mm_Vertical
J17: VCC; Molex_KK-254_AE-6410-02A_1x02_P2.54mm_Vertical
J18: Vin; Molex_KK-254_AE-6410-02A_1x02_P2.54mm_Vertical
Q1, Q3: 2N3904; TO-92_Inline_Wide
R1, R30: 10K; R_Axial_DIN0207_L6.3mm_D2.5mm_P7.62mm_Horizontal
R6, R7: 1K; R_Axial_DIN0207_L6.3mm_D2.5mm_P7.62mm_Horizontal
R8, R9, R13, R14, R18: 1k; R_Axial_DIN0207_L6.3mm_D2.5mm_P7.62mm_Horizontal
R12: 100k; R_Axial_DIN0207_L6.3mm_D2.5mm_P7.62mm_Horizontal
R15: 1M; R_Axial_DIN0207_L6.3mm_D2.5mm_P7.62mm_Horizontal
R16: 10k; R_Axial_DIN0207_L6.3mm_D2.5mm_P7.62mm_Horizontal
U1: MCP4922; DIP-14_W7.62mm_Socket_LongPads
U2: TL972; DIP-8_W7.62mm_Socket_LongPads

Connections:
+12V: A1.30, C3.1, C7.1, D13.1, U2.8
/Arduino/A_IN_A: A1.19, D1.2, D2.1, R13.1
/Arduino/A_IN_B: A1.20, D3.2, D4.1, R14.1
/Arduino/A_IN_C: A1.21, D5.2, D6.1, R18.1
/Arduino/DAC_CS: A1.13, R30.2, U1.3
/Arduino/D_IN_A: A1.5, Q3.3, R16.1
/Arduino/D_OUT_A: A1.9, R8.2
/Arduino/MOSI: A1.14, U1.5
/Arduino/SCK: A1.16, U1.4
/CV out/CV_OUT_A: J3.1, R6.2
/CV out/CV_OUT_B: J4.1, R7.2
/CV out/DAC_A: U1.14, U2.3
/CV out/DAC_B: U1.10, U2.5
/Gate out/GATE_OUT: J5.1, Q1.3, R9.1
/Inputs/CV in A/CV_IN: J11.1, R13.2
/Inputs/CV in B/CV_IN: J12.1, R14.2
/Inputs/CV in C/CV_IN: J13.1, R18.2
/Inputs/Gate in A/GATE_IN: J7.1, R12.2
GND: A1.4, A1.29, C1.2, C2.2, C3.2, C7.2, D2.2, D4.2, D6.2, J3.2, J4.2, J5.2, J7.2, J11.2, J12.2, J13.2, J17.2, J18.2, Q1.1, Q3.1, R15.1, U1.8, U1.12, U2.4
unnamed: D13.2, J18.1
unnamed: Q1.2, R8.1
unnamed: Q3.2, R12.1, R15.2
unnamed: R1.2, U1.9
unnamed: R6.1, U2.1, U2.2
unnamed: R7.1, U2.6, U2.7
VCC: A1.27, C1.1, C2.1, D1.1, D3.1, D5.1, J17.1, R1.1, R9.2, R16.2, R30.1, U1.1, U1.11, U1.13

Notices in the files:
hardware/dac_ino/dac_ino.kicad_pcb:
dac/ino v. 1.31 • Rich Holmes 7/2020 • from Synapse by Vincenzo Pacella • cc-by-ca
hardware/dac_ino_lite/dac_ino.kicad_pcb:
cc-by-sa
orig_hardware/KiCad/synapse.kicad_pcb:
cc-by-sa Vincenzo Pacella - 04.2016 - Berlin / rev. 1.0
